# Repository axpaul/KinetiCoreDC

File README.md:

# KinetiCoreDC

Carte de contrôle moteur basée sur un microcontrôleur **STM32G0** (STM32G070KBT6) conçue pour piloter des moteurs DC à l'aide de ponts en H intégrés **DRV8874** (Texas Instruments).

## Fonctionnalités principales

- **Microcontrôleur :** STM32G070KBT6 (ARM Cortex-M0+)
- **Driver moteur :** DRV8874 (pilotage moteur DC avec mesure de courant et protections intégrées)
- **Communication & Interfaces :**
  - Bus RS485 (transceiver THVD1400)
  - Bus I2C avec extenseur d'E/S (TCA9534A)
  - Entrées isolées / optocoupleurs (TLP2310)
- **Alimentation & Protections :**
  - Contrôleur de surtension / sous-tension et protection contre les inversions de polarité (LTC4365)
  - Régulateur LDO 3.3V (MCP1703)

## Structure du projet

- `KinetiCoreDC.kicad_pro` : Fichier de projet KiCad
- `KinetiCoreDC.kicad_sch` & `Interface.kicad_sch` : Schémas électroniques
- `KinetiCoreDC.kicad_pcb` : Routage du circuit imprimé
- `Datasheet/` : Documentation technique des composants clés
- `Library/` : Empreintes et modèles de composants

## Licence

Voir le fichier [LICENSE](LICENSE) pour plus de détails.

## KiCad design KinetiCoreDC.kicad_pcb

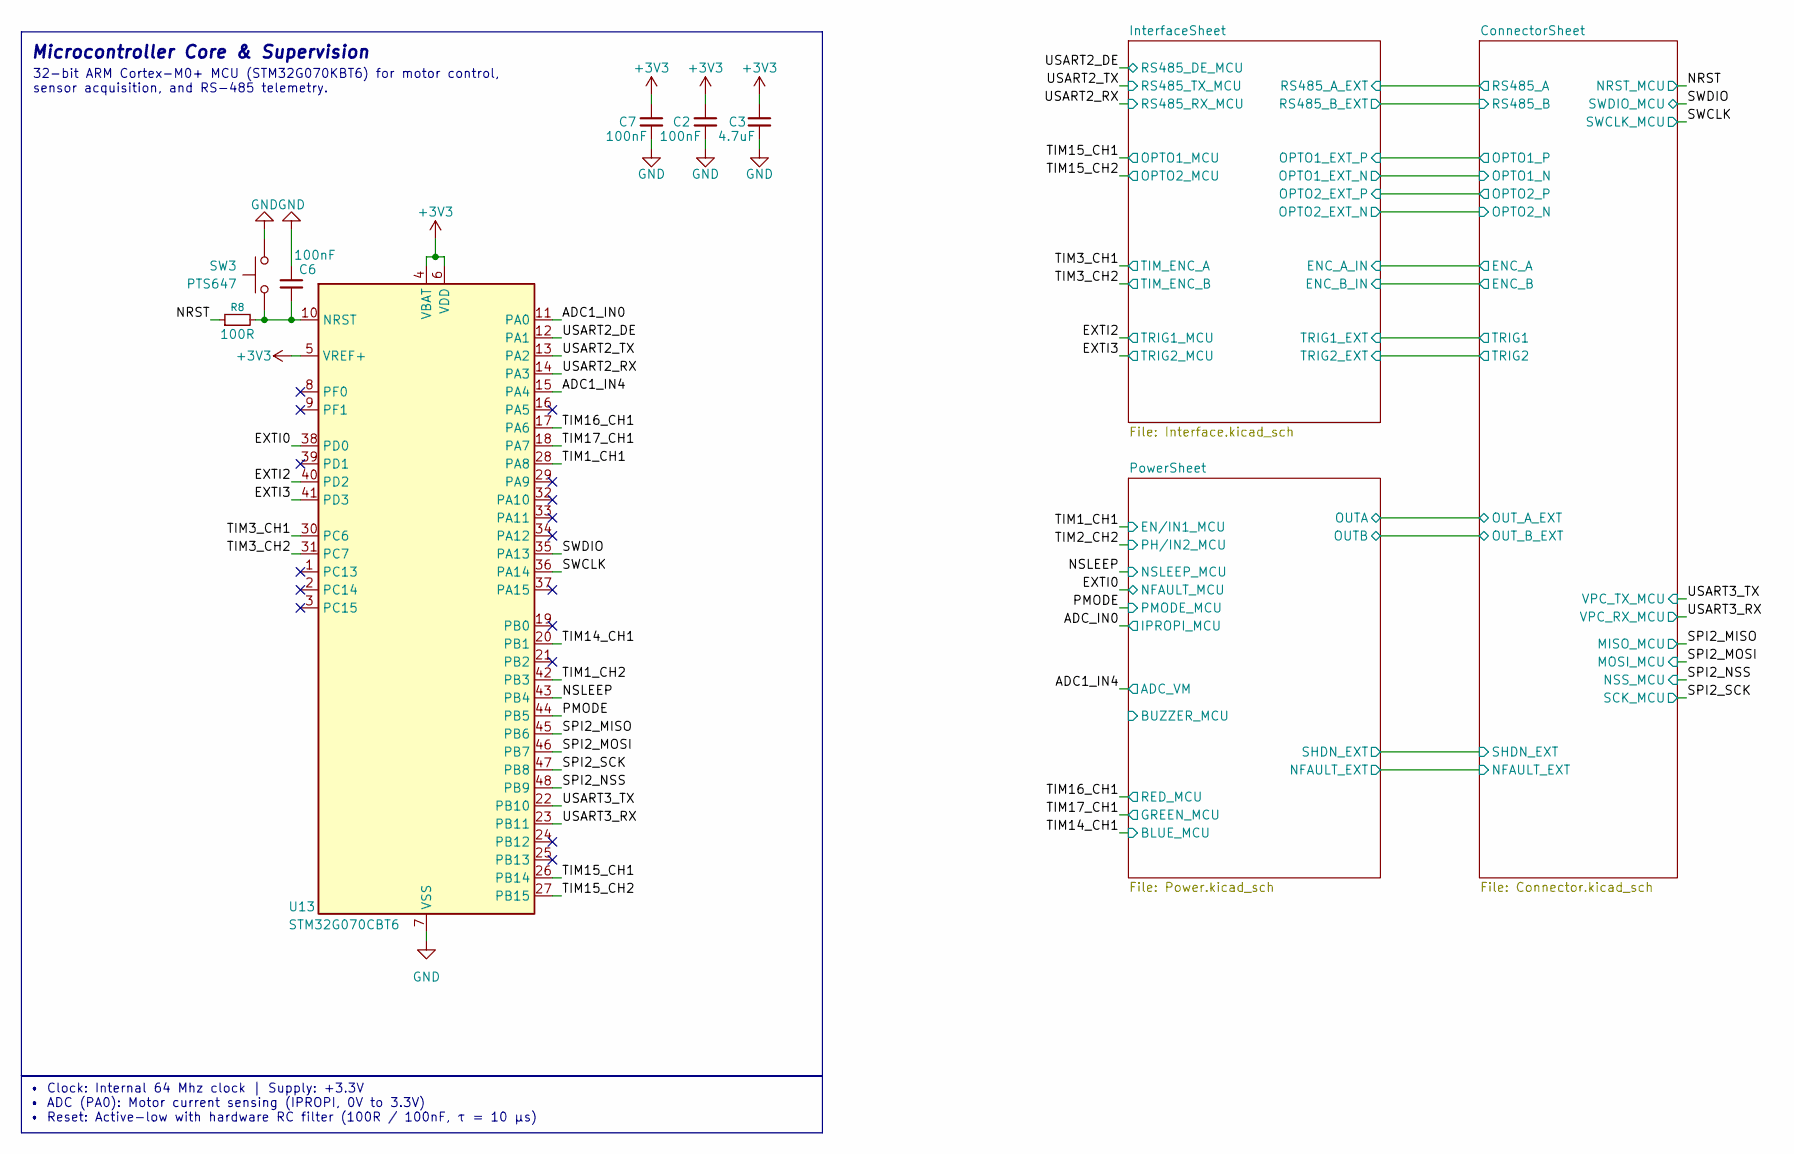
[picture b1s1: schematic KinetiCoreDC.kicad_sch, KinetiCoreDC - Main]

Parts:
C2, C6, C7: 100nF; C_0603_1608Metric
C3: 4.7uF; C_0603_1608Metric
R8: 100R; R_0603_1608Metric
SW3: PTS647; SW_SPST_PTS647_Sx38
U13: STM32G070CBT6; LQFP-48_7x7mm_P0.5mm

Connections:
+3V3: C2.1, C3.1, C7.1, U13.4 (VBAT), U13.5 (VREF+), U13.6 (VDD); also elsewhere on the board
/ADC1_IN0: U13.11 (PA0)
/ADC1_IN4: U13.15 (PA4); also elsewhere on the board
/EXTI0: U13.38 (PD0); also elsewhere on the board
/EXTI2: U13.40 (PD2); also elsewhere on the board
/EXTI3: U13.41 (PD3); also elsewhere on the board
/NRST: R8.1; also elsewhere on the board
/NSLEEP: U13.43 (PB4); also elsewhere on the board
/OE_VCP: U13.37 (PA15)
/PMODE: U13.44 (PB5); also elsewhere on the board
/SPI2_MISO: U13.45 (PB6); also elsewhere on the board
/SPI2_MOSI: U13.46 (PB7); also elsewhere on the board
/SPI2_NSS: U13.48 (PB9); also elsewhere on the board
/SPI2_SCK: U13.47 (PB8); also elsewhere on the board
/SWCLK: U13.36 (PA14); also elsewhere on the board
/SWDIO: U13.35 (PA13); also elsewhere on the board
/TIM1_CH1: U13.28 (PA8); also elsewhere on the board
/TIM1_CH2: U13.42 (PB3)
/TIM3_CH1: U13.30 (PC6); also elsewhere on the board
/TIM3_CH2: U13.31 (PC7); also elsewhere on the board
/TIM14_CH1: U13.20 (PB1); also elsewhere on the board
/TIM15_CH1: U13.26 (PB14); also elsewhere on the board
/TIM15_CH2: U13.27 (PB15); also elsewhere on the board
/TIM16_CH1: U13.17 (PA6); also elsewhere on the board
/TIM17_CH1: U13.18 (PA7); also elsewhere on the board
/USART2_DE: U13.12 (PA1); also elsewhere on the board
/USART2_RX: U13.14 (PA3); also elsewhere on the board
/USART2_TX: U13.13 (PA2); also elsewhere on the board
/USART3_RX: U13.23 (PB11); also elsewhere on the board
/USART3_TX: U13.22 (PB10); also elsewhere on the board
/VM_MONITOR_EN: U13.16 (PA5)
GND: C2.2, C3.2, C6.2, C7.2, SW3.1, U13.7 (VSS); also elsewhere on the board
unnamed: C6.1, R8.2, SW3.2, U13.10 (NRST)

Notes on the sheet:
Microcontroller Core & Supervision
32-bit ARM Cortex-M0+ MCU (STM32G070KBT6) for motor control, sensor acquisition, and RS-485 telemetry.
• Clock: Internal 64 Mhz clock | Supply: +3.3V • ADC (PA0): Motor current sensing (IPROPI, 0V to 3.3V) • Reset: Active-low with hardware RC filter (100R / 100nF, τ = 10 µs)

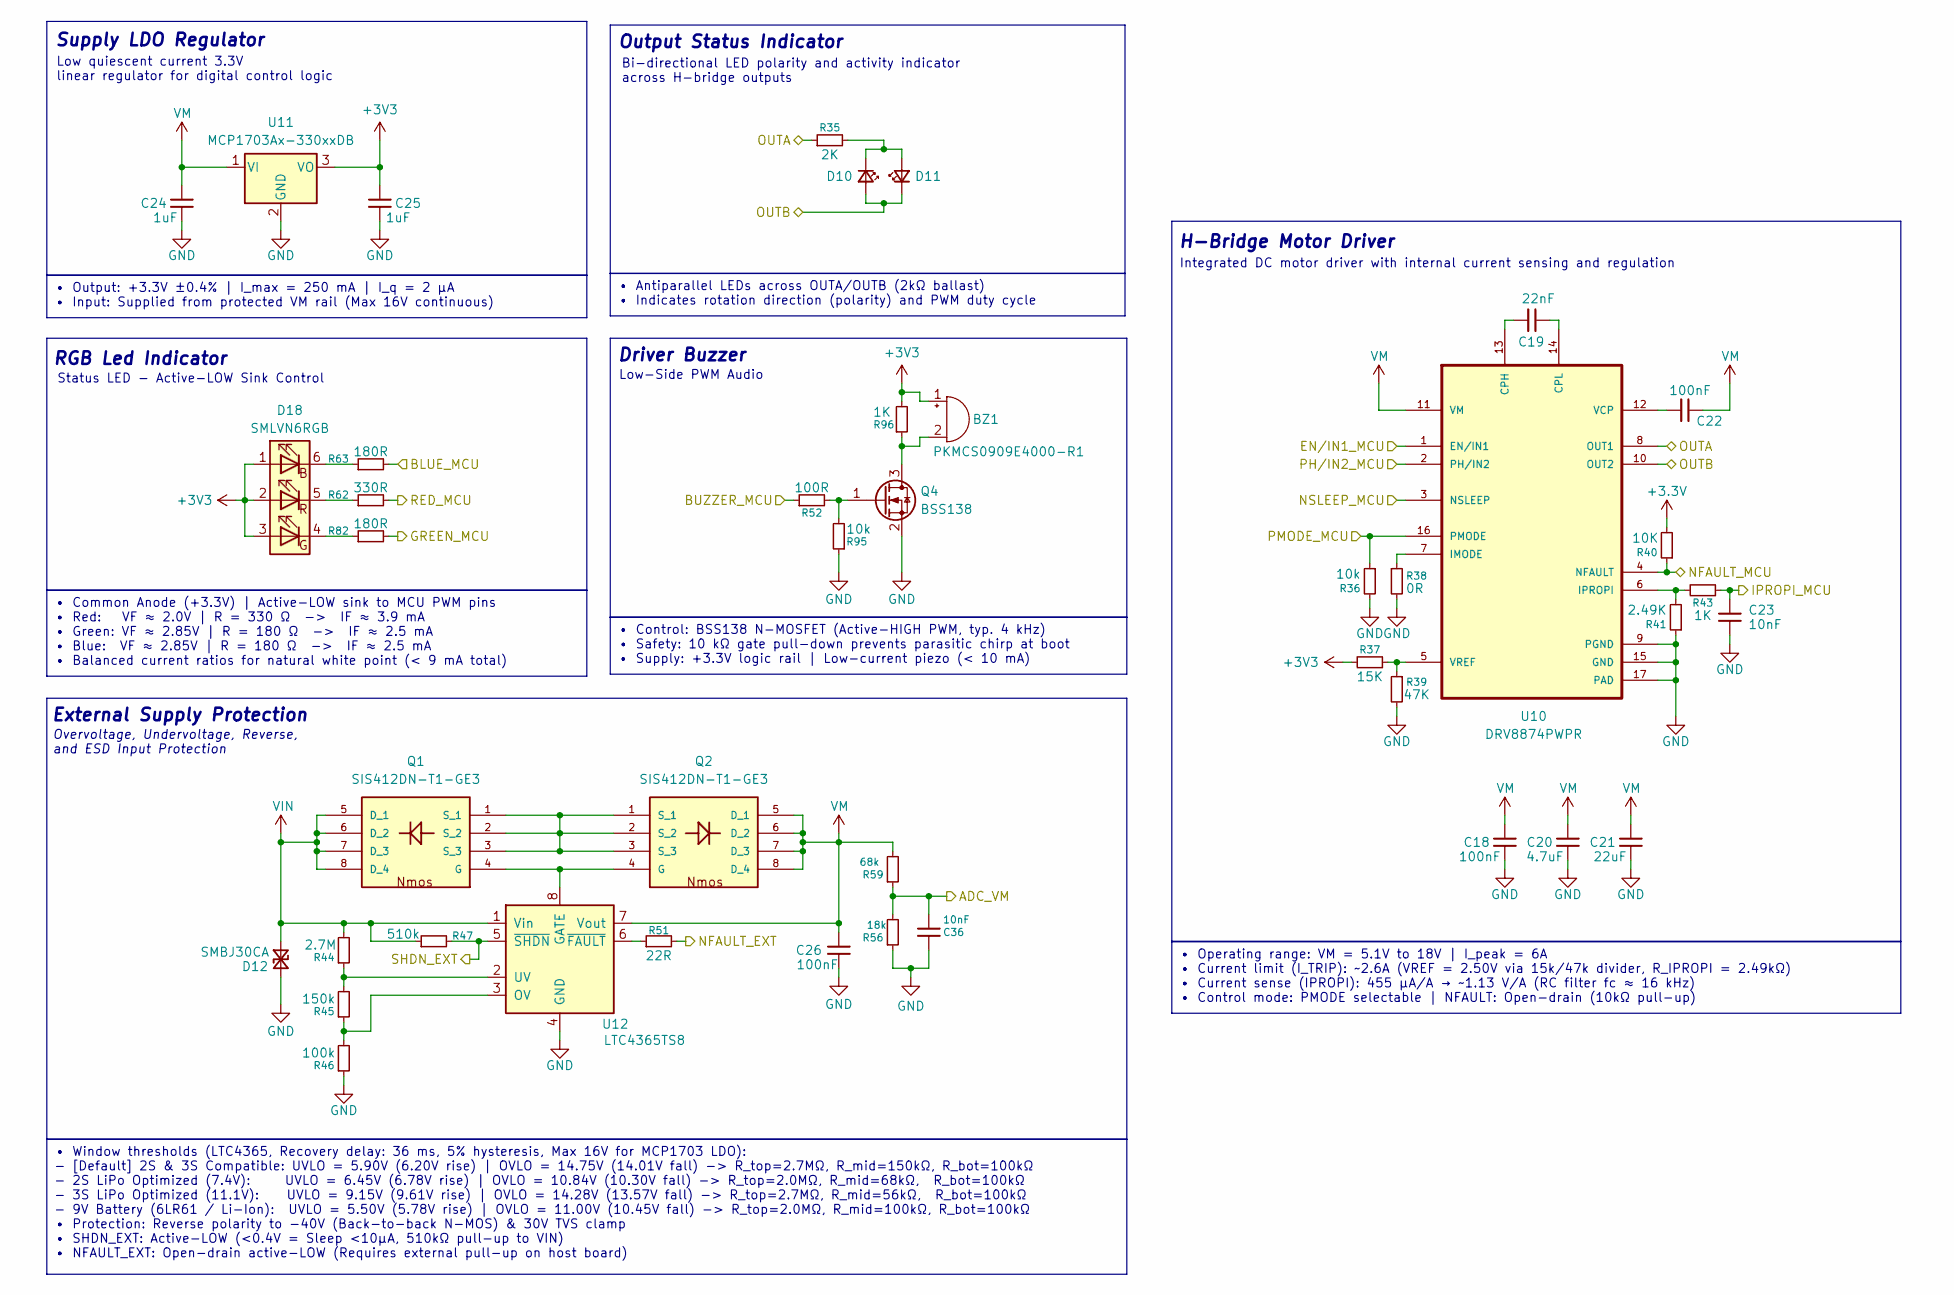
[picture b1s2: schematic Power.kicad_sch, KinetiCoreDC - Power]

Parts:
BZ1: PKMCS0909E4000-R1; Buzzer_Murata_PKMCS0909E
C18, C22, C26: 100nF; C_0603_1608Metric
C19: 22nF; C_0603_1608Metric
C20: 4.7uF; C_0805_2012Metric
C21: 22uF; C_0805_2012Metric
C23, C36: 10nF; C_0603_1608Metric
C24, C25: 1uF; C_0603_1608Metric
D10, D11: LED_Small; LED_0603_1608Metric
D12: SMBJ30CA; D_SMA
D18: SMLVN6RGB; LED_ROHM_SMLVN6
Q1, Q2: SIS412DN-T1-GE3; POWERPAK-1212-8; MOUSER_PART_NUMBER 781-SIS412DN-T1-GE3
Q4: BSS138; SOT-23
R35: 2K; R_0603_1608Metric
R36, R95: 10k; R_0603_1608Metric
R37: 15K; R_0603_1608Metric
R38: 0R; R_0603_1608Metric
R39: 47K; R_0603_1608Metric
R40: 10K; R_0603_1608Metric
R41: 2.49K; R_0603_1608Metric
R43, R96: 1K; R_0603_1608Metric
R44: 2.7M; R_0603_1608Metric
R45: 150k; R_0603_1608Metric
R46: 100k; R_0603_1608Metric
R47: 510k; R_0603_1608Metric
R51: 22R; R_0603_1608Metric
R52: 100R; R_0603_1608Metric
R56: 18k; R_0603_1608Metric
R59: 68k; R_0603_1608Metric
R62: 330R; R_0603_1608Metric
R63, R82: 180R; R_0603_1608Metric
U10: DRV8874PWPR; SOP65P640X120-17N
U11: MCP1703Ax-330xxDB; SOT-223-3_TabPin2
U12: LTC4365TS8; TSOT-23-8

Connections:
+3.3V: R40.2
+3V3: BZ1.1 (+), C25.1, D18.1 (BA), D18.2 (RA), D18.3 (GA), R37.2, R96.2, U11.3 (VO); also elsewhere on the board
/ADC1_IN4: C36.2, R56.2, R59.1; also elsewhere on the board
/ADC_IN0: C23.2, R43.1
/ConnectorSheet/NFAULT_EXT: R51.2; also elsewhere on the board
/ConnectorSheet/OUT_A_EXT: R35.1, U10.8 (OUT1); also elsewhere on the board
/ConnectorSheet/OUT_B_EXT: D10.2 (A), D11.1 (K), U10.10 (OUT2); also elsewhere on the board
/ConnectorSheet/SHDN_EXT: R47.2, U12.5 (~SHDN); also elsewhere on the board
/EXTI0: R40.1, U10.4 (NFAULT); also elsewhere on the board
/NSLEEP: U10.3 (NSLEEP); also elsewhere on the board
/PMODE: R36.1, U10.16 (PMODE); also elsewhere on the board
/PowerSheet/BUZZER_MCU: R52.1
/TIM1_CH1: U10.1 (EN/IN1); also elsewhere on the board
/TIM2_CH2: U10.2 (PH/IN2)
/TIM14_CH1: R63.2; also elsewhere on the board
/TIM16_CH1: R62.2; also elsewhere on the board
/TIM17_CH1: R82.2; also elsewhere on the board
GND: C18.2, C20.2, C21.2, C23.1, C24.2, C25.2, C26.2, C36.1, D12.2 (A2), Q4.2 (S), R36.2, R38.2, R39.2, R41.1, R46.1, R56.1, R95.1, U10.9 (PGND), U10.15 (GND), U10.17 (PAD), U11.2 (GND), U12.4 (GND); also elsewhere on the board
unnamed: BZ1.2 (-), Q4.3 (D), R96.1
unnamed: D10.1 (K), D11.2 (A), R35.2
unnamed: D18.6 (BK), R63.1
unnamed: D18.4 (GK), R82.1
unnamed: D18.5 (RK), R62.1
unnamed: Q1.4 (G), Q2.4 (G), U12.8 (GATE)
unnamed: Q1.1 (S_1), Q1.2 (S_2), Q1.3 (S_3), Q2.1 (S_1), Q2.2 (S_2), Q2.3 (S_3)
unnamed: Q4.1 (G), R52.2, R95.2
unnamed: C19.1, U10.13 (CPH)
unnamed: C19.2, U10.14 (CPL)
unnamed: R38.1, U10.7 (IMODE)
unnamed: R41.2, R43.2, U10.6 (IPROPI)
unnamed: C22.1, U10.12 (VCP)
unnamed: R37.1, R39.1, U10.5 (VREF)
unnamed: R45.1, R46.2, U12.3 (OV)
unnamed: R44.1, R45.2, U12.2 (UV)
unnamed: R51.1, U12.6 (~FAULT)
VIN: D12.1 (A1), Q1.5 (D_1), Q1.6 (D_2), Q1.7 (D_3), Q1.8 (D_4), R44.2, R47.1, U12.1 (Vin); also elsewhere on the board
VM: C18.1, C20.1, C21.1, C22.2, C24.1, C26.1, Q2.5 (D_1), Q2.6 (D_2), Q2.7 (D_3), Q2.8 (D_4), R59.2, U10.11 (VM), U11.1 (VI), U12.7 (Vout)

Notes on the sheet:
H-Bridge Motor Driver
RGB Led Indicator
Low quiescent current 3.3V linear regulator for digital control logic
Low-Side PWM Audio
Output Status Indicator
Driver Buzzer
Supply LDO Regulator
Overvoltage, Undervoltage, Reverse, and ESD Input Protection
Integrated DC motor driver with internal current sensing and regulation
External Supply Protection
Bi-directional LED polarity and activity indicator across H-bridge outputs
Status LED - Active-LOW Sink Control
• Control: BSS138 N-MOSFET (Active-HIGH PWM, typ. 4 kHz) • Safety: 10 kΩ gate pull-down prevents parasitic chirp at boot • Supply: +3.3V logic rail | Low-current piezo (< 10 mA)
• Window thresholds (LTC4365, Recovery delay: 36 ms, 5% hysteresis, Max 16V for MCP1703 LDO): - [Default] 2S & 3S Compatible: UVLO = 5.90V (6.20V rise) | OVLO = 14.75V (14.01V fall) -> R_top=2.7MΩ, R_mid=150kΩ, R_bot=100kΩ - 2S LiPo Optimized (7.4V): UVLO = 6.45V (6.78V rise) | OVLO = 10.84V (10.30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
• Output: +3.3V ±0.4% | I_max = 250 mA | I_q = 2 µA • Input: Supplied from protected VM rail (Max 16V continuous)
• Antiparallel LEDs across OUTA/OUTB (2kΩ ballast) • Indicates rotation direction (polarity) and PWM duty cycle
• Operating range: VM = 5.1V to 18V | I_peak = 6A • Current limit (I_TRIP): ~2.6A (VREF = 2.50V via 15k/47k divider, R_IPROPI = 2.49kΩ) • Current sense (IPROPI): 455 µA/A → ~1.13 V/A (RC filter fc ≈ 16 kHz) • Control mode: PMODE selectable | NFAULT: Open-drain (10kΩ pull-up)
• Common Anode (+3.3V) | Active-LOW sink to MCU PWM pins • Red: VF ≈ 2.0V | R = 330 Ω -> IF ≈ 3.9 mA • Green: VF ≈ 2.85V | R = 180 Ω -> IF ≈ 2.5 mA • Blue: VF ≈ 2.85V | R = 180 Ω -> IF ≈ 2.5 mA • Balanced current ratios for natural white point (< 9 mA total)

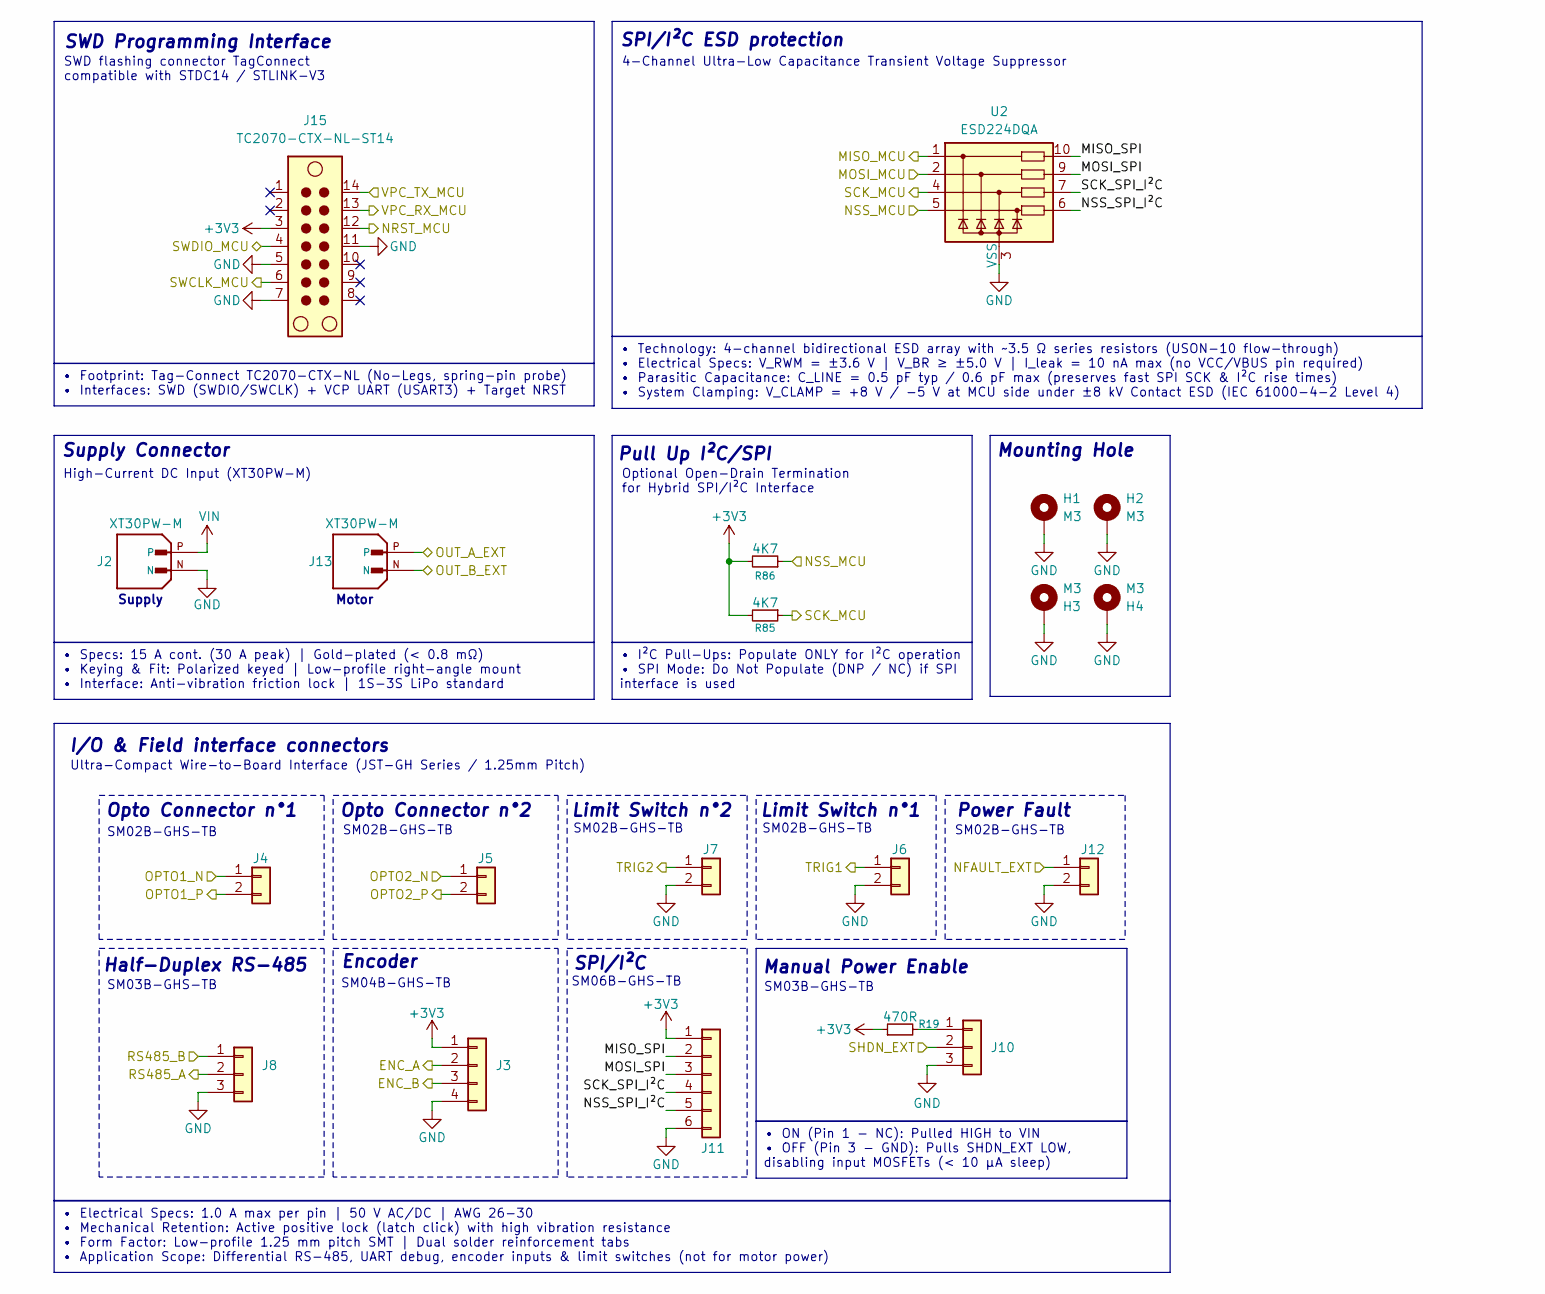
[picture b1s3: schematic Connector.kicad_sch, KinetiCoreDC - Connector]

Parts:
H1, H2, H3, H4: M3; MountingHole_3.2mm_M3_DIN965_Pad_TopBottom
J2, J13: XT30PW-M; AMASS_XT30PW-M; PARTREV 1.2
J3: SM04B-GHS-TB; JST_GH_SM04B-GHS-TB_1x04-1MP_P1.25mm_Horizontal
J4, J6, J7, J12: SM02B-GHS-TB; JST_GH_SM02B-GHS-TB_1x02-1MP_P1.25mm_Horizontal
J5: BM02B-GHS-TBT; JST_GH_SM02B-GHS-TB_1x02-1MP_P1.25mm_Horizontal
J8, J10: SM03B-GHS-TB; JST_GH_SM03B-GHS-TB_1x03-1MP_P1.25mm_Horizontal
J11: Conn_01x06; JST_GH_SM06B-GHS-TB_1x06-1MP_P1.25mm_Horizontal
J15: TC2070-CTX-NL-ST14; Tag-Connect_TC2070-IDC-FP_2x07_P1.27mm_Vertical
R19: 470R; R_0603_1608Metric
R85, R86: 4K7; R_0603_1608Metric
U2: ESD224DQA; Diodes_UDFN-10_1x2.5mm_P0.5mm

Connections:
+3V3: J3.1, J11.1, J15.3, R19.1, R85.2, R86.2; also elsewhere on the board
/ConnectorSheet/ENC_A: J3.2; also elsewhere on the board
/ConnectorSheet/ENC_B: J3.3; also elsewhere on the board
/ConnectorSheet/MISO_SPI: J11.2, U2.10
/ConnectorSheet/MOSI_SPI: J11.3, U2.9
/ConnectorSheet/NFAULT_EXT: J12.1; also elsewhere on the board
/ConnectorSheet/NSS_SPI_I²C: J11.5, U2.6
/ConnectorSheet/OPTO1_N: J4.1; also elsewhere on the board
/ConnectorSheet/OPTO1_P: J4.2; also elsewhere on the board
/ConnectorSheet/OPTO2_N: J5.1; also elsewhere on the board
/ConnectorSheet/OPTO2_P: J5.2; also elsewhere on the board
/ConnectorSheet/OUT_A_EXT: J13.P; also elsewhere on the board
/ConnectorSheet/OUT_B_EXT: J13.N; also elsewhere on the board
/ConnectorSheet/RS485_A: J8.2; also elsewhere on the board
/ConnectorSheet/RS485_B: J8.1; also elsewhere on the board
/ConnectorSheet/SCK_SPI_I²C: J11.4, U2.7
/ConnectorSheet/SHDN_EXT: J10.2; also elsewhere on the board
/ConnectorSheet/TRIG1: J6.1; also elsewhere on the board
/ConnectorSheet/TRIG2: J7.1; also elsewhere on the board
/NRST: J15.12; also elsewhere on the board
/SPI2_MISO: U2.1; also elsewhere on the board
/SPI2_MOSI: U2.2; also elsewhere on the board
/SPI2_NSS: R86.1, U2.5; also elsewhere on the board
/SPI2_SCK: R85.1, U2.4; also elsewhere on the board
/SWCLK: J15.6; also elsewhere on the board
/SWDIO: J15.4; also elsewhere on the board
/USART3_RX: J15.13; also elsewhere on the board
/USART3_TX: J15.14; also elsewhere on the board
GND: H1.1 (1_1), H2.1 (1_1), H3.1 (1_1), H4.1 (1_1), J2.N, J3.4, J6.2, J7.2, J8.3, J10.3, J11.6, J12.2, J15.5, J15.7, J15.11, U2.3 (VSS), U2.8 (VSS); also elsewhere on the board
unnamed: J10.1, R19.2
VIN: J2.P; also elsewhere on the board

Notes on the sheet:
Limit Switch n°1
Pull Up I²C/SPI
SM03B-GHS-TB
Encoder
Power Fault
I/O & Field interface connectors
Optional Open-Drain Termination for Hybrid SPI/I²C Interface
SPI/I²C
Opto Connector n°1
SM06B-GHS-TB
High-Current DC Input (XT30PW-M)
SM02B-GHS-TB
SWD flashing connector TagConnect compatible with STDC14 / STLINK-V3
4-Channel Ultra-Low Capacitance Transient Voltage Suppressor
Limit Switch n°2
Opto Connector n°2
Mounting Hole
SM04B-GHS-TB
Manual Power Enable
Ultra-Compact Wire-to-Board Interface (JST-GH Series / 1.25mm Pitch)
SPI/I²C ESD protection
Half-Duplex RS-485
Supply Connector
SWD Programming Interface
Supply
Motor
• Footprint: Tag-Connect TC2070-CTX-NL (No-Legs, spring-pin probe) • Interfaces: SWD (SWDIO/SWCLK) + VCP UART (USART3) + Target NRST
• Electrical Specs: 1.0 A max per pin | 50 V AC/DC | AWG 26-30 • Mechanical Retention: Active positive lock (latch click) with high vibration resistance • Form Factor: Low-profile 1.25 mm pitch SMT | Dual solder reinforcement tabs • Application Scope: Differential RS-485, UART debug, encoder inputs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
• Specs: 15 A cont. (30 A peak) | Gold-plated (< 0.8 mΩ) • Keying & Fit: Polarized keyed | Low-profile right-angle mount • Interface: Anti-vibration friction lock | 1S-3S LiPo standard
• Technology: 4-channel bidirectional ESD array with ~3.5 Ω series resistors (USON-10 flow-through) • Electrical Specs: V_RWM = ±3.6 V | V_BR ≥ ±5.0 V | I_leak = 10 nA max (no VCC/VBUS pin required) • Parasitic Capacitance: C_LINE = 0.5 pF typ / 0.6 pF max (preserves fast SPI SCK & I²C rise times) 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
• I²C Pull-Ups: Populate ONLY for I²C operation • SPI Mode: Do Not Populate (DNP / NC) if SPI interface is used
• ON (Pin 1 - NC): Pulled HIGH to VIN • OFF (Pin 3 - GND): Pulls SHDN_EXT LOW, disabling input MOSFETs (< 10 µA sleep)

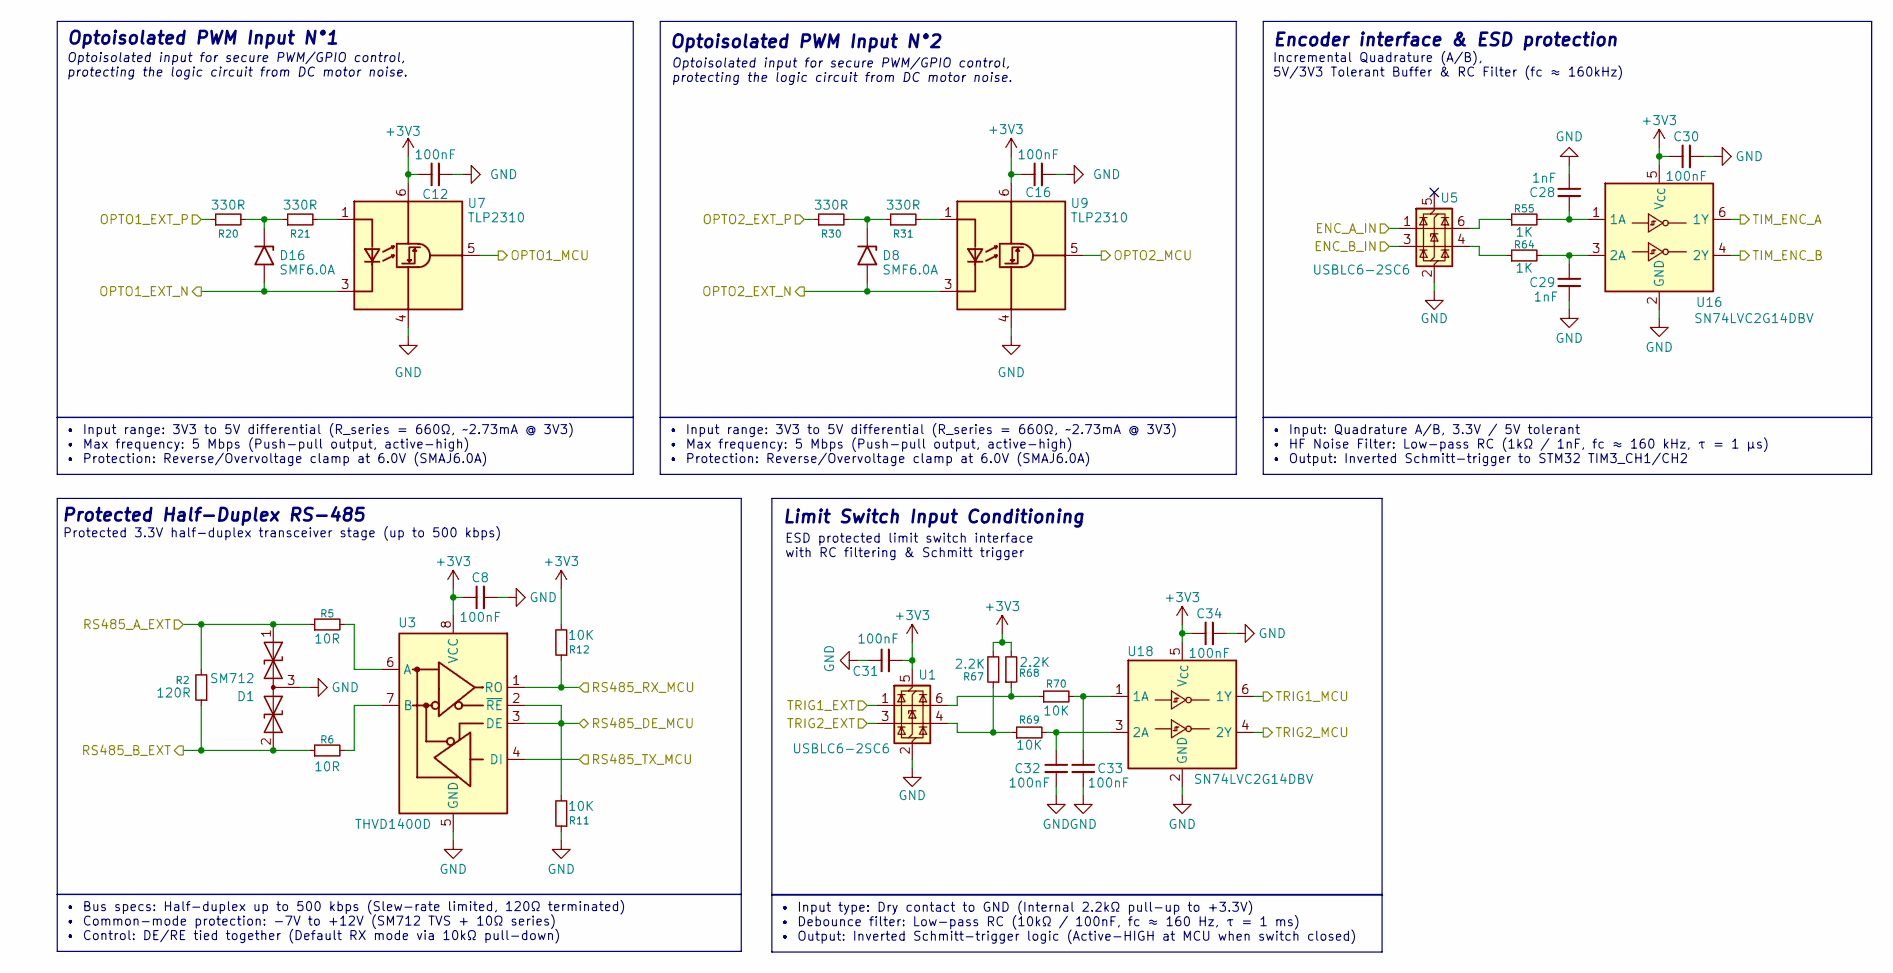
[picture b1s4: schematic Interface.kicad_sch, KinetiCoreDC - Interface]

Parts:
C8, C12, C16, C30, C31, C32, C33, C34: 100nF; C_0603_1608Metric
C28, C29: 1nF; C_0603_1608Metric
D1: SM712; SOT-23
D8, D16: SMF6.0A; D_SOD-123F
R2: 120R; R_0603_1608Metric
R5, R6: 10R; R_0603_1608Metric
R11, R12, R69, R70: 10K; R_0603_1608Metric
R20, R21, R30, R31: 330R; R_0603_1608Metric
R55, R64: 1K; R_0603_1608Metric
R67, R68: 2.2K; R_0603_1608Metric
U1, U5: USBLC6-2SC6; SOT-23-6
U3: THVD1400D; SOIC-8_3.9x4.9mm_P1.27mm
U7, U9: TLP2310; SO-5-6_4.55x3.7mm_P1.27mm
U16, U18: SN74LVC2G14DBV; SOT-23-6

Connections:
+3V3: C8.1, C12.1, C16.1, C30.1, C31.1, C34.1, R12.2, R67.2, R68.2, U1.5 (VBUS), U3.8 (VCC), U7.6 (VDD), U9.6 (VDD), U16.5 (V_{CC}), U18.5 (V_{CC}); also elsewhere on the board
/ConnectorSheet/ENC_A: U5.1 (I/O1); also elsewhere on the board
/ConnectorSheet/ENC_B: U5.3 (I/O2); also elsewhere on the board
/ConnectorSheet/OPTO1_N: D16.2 (A2), U7.3 (K); also elsewhere on the board
/ConnectorSheet/OPTO1_P: R20.1; also elsewhere on the board
/ConnectorSheet/OPTO2_N: D8.2 (A2), U9.3 (K); also elsewhere on the board
/ConnectorSheet/OPTO2_P: R30.1; also elsewhere on the board
/ConnectorSheet/RS485_A: D1.1 (A1), R2.2, R5.1; also elsewhere on the board
/ConnectorSheet/RS485_B: D1.2 (A2), R2.1, R6.1; also elsewhere on the board
/ConnectorSheet/TRIG1: U1.3 (I/O2); also elsewhere on the board
/ConnectorSheet/TRIG2: U1.1 (I/O1); also elsewhere on the board
/EXTI2: U18.6 (1Y); also elsewhere on the board
/EXTI3: U18.4 (2Y); also elsewhere on the board
/TIM3_CH1: U16.6 (1Y); also elsewhere on the board
/TIM3_CH2: U16.4 (2Y); also elsewhere on the board
/TIM15_CH1: U7.5 (VO); also elsewhere on the board
/TIM15_CH2: U9.5 (VO); also elsewhere on the board
/USART2_DE: R11.2, U3.2 (~RE), U3.3 (DE); also elsewhere on the board
/USART2_RX: R12.1, U3.1 (RO); also elsewhere on the board
/USART2_TX: U3.4 (DI); also elsewhere on the board
GND: C8.2, C12.2, C16.2, C28.1, C29.1, C30.2, C31.2, C32.1, C33.1, C34.2, D1.3 (common), R11.1, U1.2 (GND), U3.5 (GND), U5.2 (GND), U7.4 (GND), U9.4 (GND), U16.2 (GND), U18.2 (GND); also elsewhere on the board
unnamed: D8.1 (A1), R30.2, R31.1
unnamed: D16.1 (A1), R20.2, R21.1
unnamed: R55.1, U5.6 (I/O1)
unnamed: R64.1, U5.4 (I/O2)
unnamed: R67.1, R69.1, U1.4 (I/O2)
unnamed: R68.1, R70.1, U1.6 (I/O1)
unnamed: R5.2, U3.6 (A)
unnamed: R6.2, U3.7 (B)
unnamed: R21.2, U7.1 (A)
unnamed: R31.2, U9.1 (A)
unnamed: C28.2, R55.2, U16.1 (1A)
unnamed: C29.2, R64.2, U16.3 (2A)
unnamed: C33.2, R70.2, U18.1 (1A)
unnamed: C32.2, R69.2, U18.3 (2A)

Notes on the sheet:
Optoisolated PWM Input N°1
Protected 3.3V half-duplex transceiver stage (up to 500 kbps)
Optoisolated input for secure PWM/GPIO control, protecting the logic circuit from DC motor noise.
Incremental Quadrature (A/B), 5V/3V3 Tolerant Buffer & RC Filter (fc ≈ 160kHz)
Encoder interface & ESD protection
Limit Switch Input Conditioning
ESD protected limit switch interface with RC filtering & Schmitt trigger
Optoisolated PWM Input N°2
Protected Half-Duplex RS-485
• Input: Quadrature A/B, 3.3V / 5V tolerant • HF Noise Filter: Low-pass RC (1kΩ / 1nF, fc ≈ 160 kHz, τ = 1 µs) • Output: Inverted Schmitt-trigger to STM32 TIM3_CH1/CH2
• Bus specs: Half-duplex up to 500 kbps (Slew-rate limited, 120Ω terminated) • Common-mode protection: -7V to +12V (SM712 TVS + 10Ω series) • Control: DE/RE tied together (Default RX mode via 10kΩ pull-down)
• Input type: Dry contact to GND (Internal 2.2kΩ pull-up to +3.3V) • Debounce filter: Low-pass RC (10kΩ / 100nF, fc ≈ 160 Hz, τ = 1 ms) • Output: Inverted Schmitt-trigger logic (Active-HIGH at MCU when switch closed)
• Input range: 3V3 to 5V differential (R_series = 660Ω, ~2.73mA @ 3V3) • Max frequency: 5 Mbps (Push-pull output, active-high) • Protection: Reverse/Overvoltage clamp at 6.0V (SMAJ6.0A)

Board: 2 copper layers, 104 parts (12 on the bottom side), 82 nets, no tracks yet.

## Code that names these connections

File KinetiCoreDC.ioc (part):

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Mcu.Name=STM32G070CBTx
Mcu.Package=LQFP48
Mcu.UserName=STM32G070CBTx
PA0.GPIOParameters=GPIO_Label
PA0.GPIO_Label=IPROPI
PA0.Mode=IN0
PA0.Signal=ADC1_IN0
PA1.GPIOParameters=GPIO_Label
PA1.GPIO_Label=RS485_DE
PA1.Mode=Hardware Flow Control (RS485)
PA1.Signal=USART2_DE
PA13.Mode=Serial_Wire
PA13.Signal=SYS_SWDIO
PA14-BOOT0.Mode=Serial_Wire
PA14-BOOT0.Signal=SYS_SWCLK
PA15.GPIOParameters=GPIO_Label
PA15.GPIO_Label=OE_VCP
PA15.Signal=GPIO_Output
PA2.GPIOParameters=GPIO_Label
PA2.GPIO_Label=RS485_TX
PA2.Mode=Asynchronous
PA2.Signal=USART2_TX
PA3.GPIOParameters=GPIO_Label
PA3.GPIO_Label=RS485_RX
PA3.Mode=Asynchronous
PA3.Signal=USART2_RX
PA4.GPIOParameters=GPIO_Label
PA4.GPIO_Label=ADC_VM
PA4.Mode=IN4
PA4.Signal=ADC1_IN4
PA5.GPIOParameters=GPIO_Label
PA5.GPIO_Label=VM_MONITOR_EN
PA5.Signal=GPIO_Output
PA6.GPIOParameters=GPIO_Label
PA6.GPIO_Label=RED_RGB
PA6.Signal=S_TIM16_CH1
PA7.GPIOParameters=GPIO_Label
PA7.GPIO_Label=GREEN_RGB
PA7.Signal=S_TIM17_CH1
PA8.GPIOParameters=GPIO_Label
PA8.GPIO_Label=EN/IN1_DRV
PA8.Signal=S_TIM1_CH1
PB1.GPIOParameters=GPIO_Label
PB1.GPIO_Label=BLUE_RGB
PB1.Signal=S_TIM14_CH1
PB10.GPIOParameters=GPIO_Label
PB10.GPIO_Label=VCP_TX
PB10.Mode=Asynchronous
PB10.Signal=USART3_TX
PB11.GPIOParameters=GPIO_Label
PB11.GPIO_Label=VCP_RX
PB11.Mode=Asynchronous
PB11.Signal=USART3_RX
PB14.GPIOParameters=GPIO_Label
PB14.GPIO_Label=OPTO1
PB14.Signal=S_TIM15_CH1
PB15.GPIOParameters=GPIO_Label
PB15.GPIO_Label=OPTO2
PB15.Signal=S_TIM15_CH2
PB3.Signal=S_TIM1_CH2
PB4.GPIOParameters=GPIO_Label
PB4.GPIO_Label=NSLEEP
PB4.Signal=GPIO_Output
PB5.GPIOParameters=GPIO_Label
PB5.GPIO_Label=PMODE
PB5.Signal=GPIO_Output
PB6.Mode=Full_Duplex_Master
PB6.Signal=SPI2_MISO
PB7.Mode=Full_Duplex_Master
PB7.Signal=SPI2_MOSI
PB8.Mode=Full_Duplex_Master
PB8.Signal=SPI2_SCK
PB9.Mode=NSS_Signal_Hard_Output
PB9.Signal=SPI2_NSS
PC6.GPIOParameters=GPIO_Label
PC6.GPIO_Label=TIM_ENC_A
PC6.Signal=S_TIM3_CH1
PC7.GPIOParameters=GPIO_Label
PC7.GPIO_Label=TIM_ENC_B
PC7.Signal=S_TIM3_CH2
PD0.GPIOParameters=GPIO_Label
PD0.GPIO_Label=NFAULT_DRV
PD0.Signal=GPXTI0
PD2.GPIOParameters=GPIO_Label
PD2.GPIO_Label=TRIG1
PD2.Signal=GPXTI2
PD3.GPIOParameters=GPIO_Label
PD3.GPIO_Label=TRIG2
PD3.Signal=GPXTI3
PF0-OSC_IN\ (PF0).Mode=HSE-External-Oscillator
PF0-OSC_IN\ (PF0).Signal=RCC_OSC_IN
PF1-OSC_OUT\ (PF1).Mode=HSE-External-Oscillator
PF1-OSC_OUT\ (PF1).Signal=RCC_OSC_OUT
RCC.HSE_VALUE=8000000
RCC.SYSCLKFreq_VALUE=16000000
board=custom
